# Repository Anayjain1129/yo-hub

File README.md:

# Yo-hub
So, I personally have a laptop and I really nedd more ports cause I only have 2 Type-A and a Type-C and after getting my hackpad I dont have any ports left, so here it comes Yo-Hub

# Sch & PCB
It was really frustrating part but yea I asked for help from hackclubbers and yea they really helped me also the guide on jams.hackclub.com helped me

#  Schematic

# PCB

# CAD
Okay so it was really good time doing im really getting good at it.

# Front

# Bottom

# Whole

# BOM

| Name                                                          | Qty | Final Price - INR (USD) | Link                                                                                                                        |
| ------------------------------------------------------------- | --- | ----------------------- | ----------------------------------------------------------------------------------------------------------                  |
| PCBA                                                          | 2   | 2,630 ($30.4)           |                                                                                                                             |
| PCB                                                           | 5   | 1210.01 ($14.16)        |                                                                                                                             |
| M2 x 6mm Screws                                               | 25  | 212  ($2.42)            | [here](https://www.amazon.in/dp/B08BXVGLVW?ref_=cm_sw_r_cp_ud_dp_T2FF463SH3DMFF4E48Z5&previewDohEventScheduleTesting=C)     |
| M2 Nuts                                                       | 50  | 250 ($2.85)             | [here](https://www.amazon.in/dp/B0CW6KWSV6?ref_=cm_sw_r_cp_ud_dp_8R0WDQ3BTDCMJ3MX2EB8&previewDohEventScheduleTesting=C)     |
| Top Case                                                      | 1   | NA                      | Print Legion                                                                                                                |
| Bottom Case                                                   | 1   | NA                      | Print Legion                                                                                                                |

## Total Pricing

The cost of all the parts comes out to be $49.65, but there are gonna be cost of shipping so the Total Cost is ~$60

All together The total Cost is 60$

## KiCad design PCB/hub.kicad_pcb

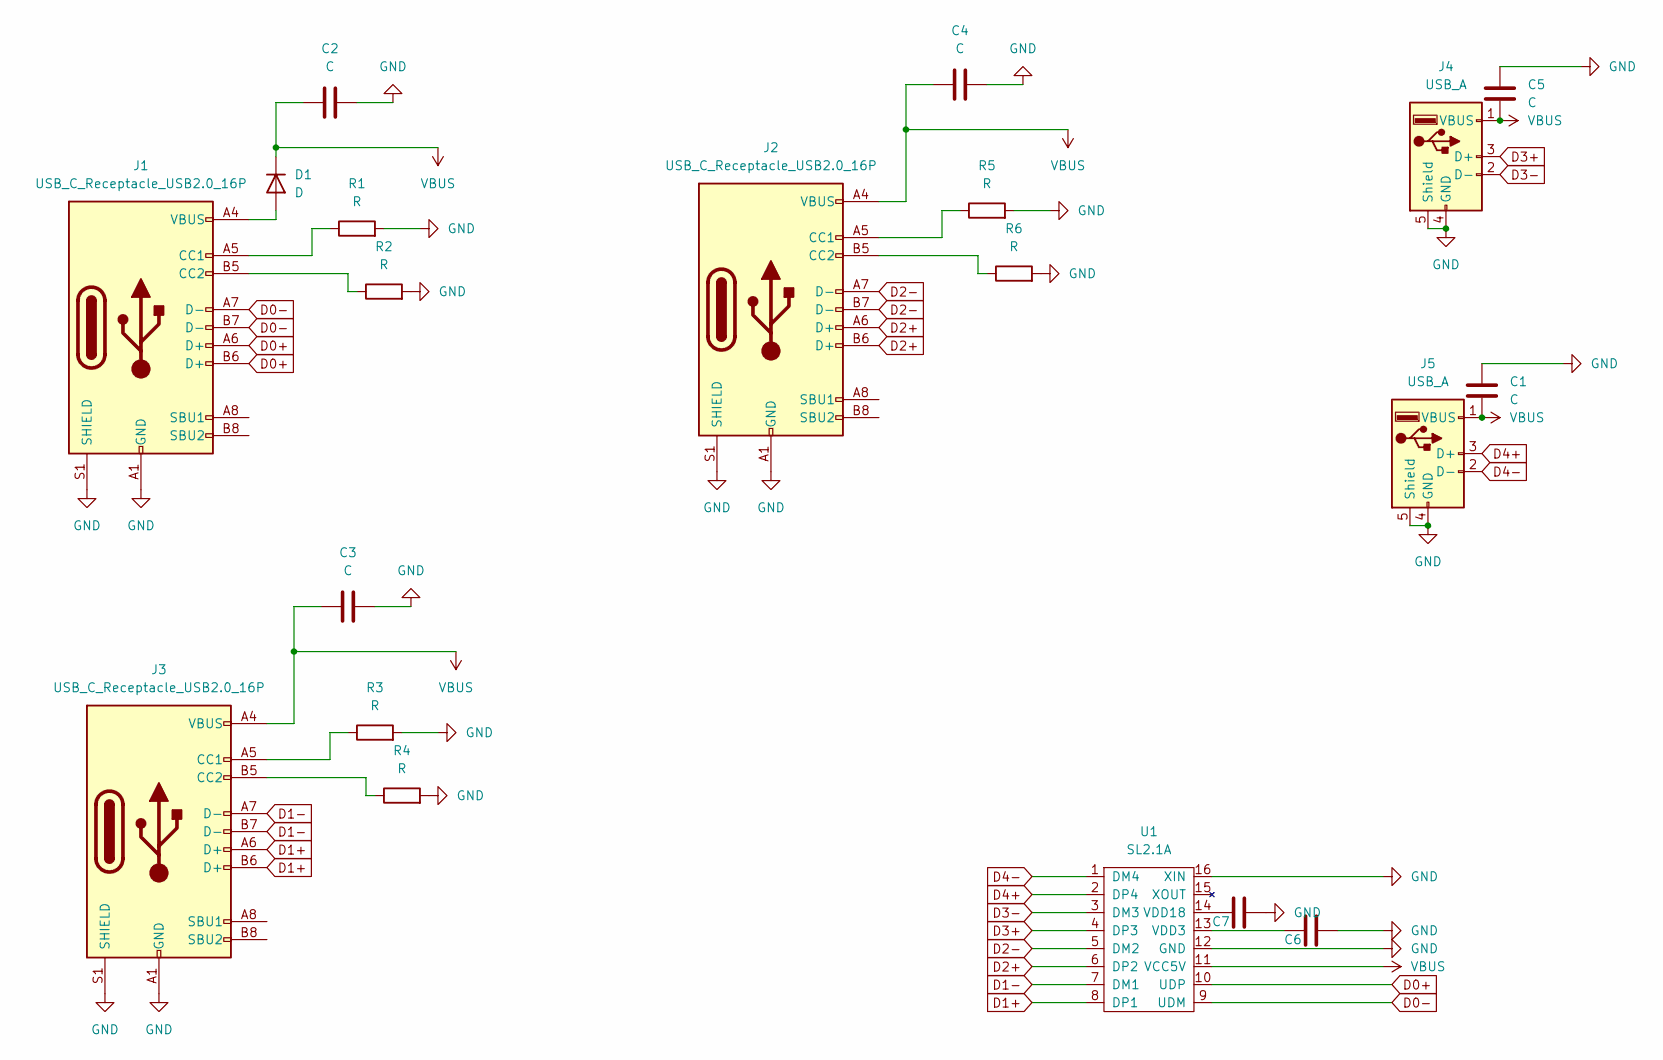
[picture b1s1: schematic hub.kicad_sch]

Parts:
C1, C2, C3, C4, C5: C; C_0805_2012Metric
C6, C7: 10uF; C_0805_2012Metric; LCSC C48579582
D1: D; D_SMA
J1, J2, J3: USB_C_Receptacle_USB2.0_16P; USB_C_Receptacle_G-Switch_GT-USB-7010ASV
J4, J5: USB_A; USB_A_Receptacle_GCT_USB1046
R1, R2, R3, R4, R5, R6: R; R_0805_2012Metric
U1: SL2.1A; SOIC-16_4.55x10.3mm_P1.27mm

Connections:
D0+: J1.A6 (D+), J1.B6 (D+), U1.10 (UDP)
D0-: J1.A7 (D-), J1.B7 (D-), U1.9 (UDM)
D1+: J3.A6 (D+), J3.B6 (D+), U1.8 (DP1)
D1-: J3.A7 (D-), J3.B7 (D-), U1.7 (DM1)
D2+: J2.A6 (D+), J2.B6 (D+), U1.6 (DP2)
D2-: J2.A7 (D-), J2.B7 (D-), U1.5 (DM2)
D3+: J4.3 (D+), U1.4 (DP3)
D3-: J4.2 (D-), U1.3 (DM3)
D4+: J5.3 (D+), U1.2 (DP4)
D4-: J5.2 (D-), U1.1 (DM4)
GND: C1.1, C2.1, C3.1, C4.1, C5.1, C6.2, C7.2, J1.A1 (GND), J1.A12 (GND), J1.B1 (GND), J1.B12 (GND), J1.S1 (SHIELD), J2.A1 (GND), J2.A12 (GND), J2.B1 (GND), J2.B12 (GND), J2.S1 (SHIELD), J3.A1 (GND), J3.A12 (GND), J3.B1 (GND), J3.B12 (GND), J3.S1 (SHIELD), J4.4 (GND), J4.5 (Shield), J5.4 (GND), J5.5 (Shield), R1.2, R2.2, R3.2, R4.2, R5.2, R6.2, U1.12 (GND), U1.16 (XIN)
unnamed: D1.2 (A), J1.A4 (VBUS), J1.A9 (VBUS), J1.B4 (VBUS), J1.B9 (VBUS)
unnamed: J1.A5 (CC1), R1.1
unnamed: J1.B5 (CC2), R2.1
unnamed: J2.A5 (CC1), R5.1
unnamed: J2.B5 (CC2), R6.1
unnamed: J3.A5 (CC1), R3.1
unnamed: J3.B5 (CC2), R4.1
unnamed: C6.1, U1.13 (VDD3)
unnamed: C7.1, U1.14 (VDD18)
VBUS: C1.2, C2.2, C3.2, C4.2, C5.2, D1.1 (K), J2.A4 (VBUS), J2.A9 (VBUS), J2.B4 (VBUS), J2.B9 (VBUS), J3.A4 (VBUS), J3.A9 (VBUS), J3.B4 (VBUS), J3.B9 (VBUS), J4.1 (VBUS), J5.1 (VBUS), U1.11 (VCC5V)

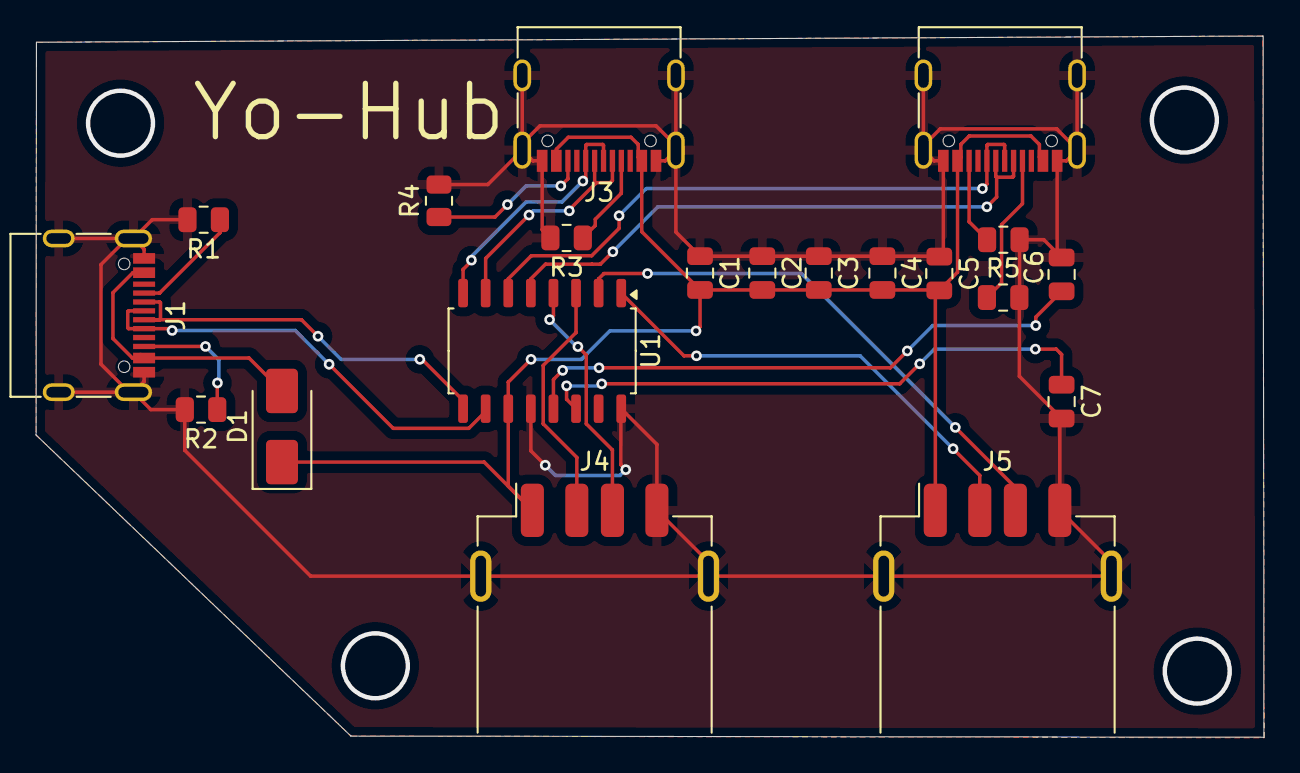
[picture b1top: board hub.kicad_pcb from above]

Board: 2 copper layers, 69.0 x 39.4 mm, 20 parts (0 on the bottom side), 21 nets.
